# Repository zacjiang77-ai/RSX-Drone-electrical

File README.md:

# RSX Jetson 19 V buck converter

This is a standalone daughterboard for the protected 6S branch of the RSX PDB. Open `RSX_Jetson_19V.kicad_pro` in KiCad 9 or later. Keep both project library tables and the project-local symbol and footprint libraries alongside the project.

| Parameter | Design value |
| --- | --- |
| Input at U1 under load | 19.8–25.2 V DC |
| Output | 19.0 V nominal |
| Jetson load assumption | 2.37 A, 45.0 W |
| Power-stage design target | 3.0 A, 57 W |
| Topology | LM70880RRXR synchronous buck |
| Switching frequency | 220 kHz nominal with 100 kΩ at RT |
| Board | 64 × 39 mm, four copper layers, four 3.2 mm mounting holes |

## Wiring

- J1 pin 1 takes protected 6S VBAT. J1 pin 2 is ground. Use the upstream protection and cutoff provided by the PDB. U1 EN follows the input and supplies no separate 6S cutoff.
- J2 pin 1 supplies +19 V to the center contact of the Jetson cable. J2 pin 2 goes to the barrel sleeve. Verify polarity at the actual cable before plugging in the Jetson.
- The board assumes the specified 19.8 V minimum at the regulator pins after cable and PDB losses.

## Design calculations

- Feedback setpoint is 0.8 V × (1 + 232 kΩ / 10.2 kΩ) = 18.996 V nominal.
- TI's off-time equation gives 19.59 V at 240 kHz and 126 ns. At 19.8 V there is approximately 0.21 V of margin before conduction losses, setpoint tolerance and ripple. In low-dropout mode the regulator can skip off cycles. Steady regulation at the 3 A target remains subject to bench validation.
- L1 is 33 µH nominal, with a specified maximum DCR of 20.7 mΩ at 25 °C. Ideal inductor ripple at 25.2 V is about 0.64 A peak-to-peak at 220 kHz and nominal inductance. U1 senses across the 10 mΩ shunt with separate Kelvin connections. The nominal cycle-by-cycle threshold is 5.6 A of peak inductor current.
- The Type II compensation network starts at 8.06 kΩ, 33 nF and 820 pF. It targets approximately 5.4 kHz crossover using TI's simplified calculation with 120 µF effective output capacitance. Actual DC bias, ESR and crossover need verification with the assembled output network.
- SW4 is internally connected to the switching node and is routed locally to the bootstrap capacitor. The main switch path uses SW1 through SW3.

## Layout and bring-up

1. Review the RRX0029B land pattern and stencil with the assembler. Specify filled and capped vias where they are inside solderable pads, including the ground thermal pad. Align L1's marked winding-start terminal with pad 1 toward U1.
2. Use a current-limited bench source and an electronic load. Start at 22.2 V and verify polarity, startup, and no-load output. Sweep input from 25.2 V to 19.8 V while checking 2.37 A and then the 3 A design target.
3. Scope VIN at U1 and VOUT at the Jetson cable during input and load steps. Check ripple, hot operation, loop response and recovery near dropout. Keep startup and unload peaks below the Jetson's 20 V DC jack maximum. Verify with the real battery, PDB and cable before flight.

KiCad 9.0.2 ERC, board DRC and schematic parity checks pass. Hardware testing is pending.

## References

- [TI LM70880 datasheet and RRX0029B package drawing](https://www.ti.com/lit/ds/symlink/lm70880.pdf)
- [Coilcraft XGL1313-333 inductor specifications and land pattern](https://www.coilcraft.com/en-us/products/power/high-voltage-inductors/xgl/xgl1313/xgl1313-333/)
- [NVIDIA Jetson Orin Nano developer kit carrier board specification](https://developer.nvidia.com/downloads/assets/embedded/secure/jetson/orin_nano/docs/jetson_orin_nano_devkit_carrier_board_specification_sp.pdf)

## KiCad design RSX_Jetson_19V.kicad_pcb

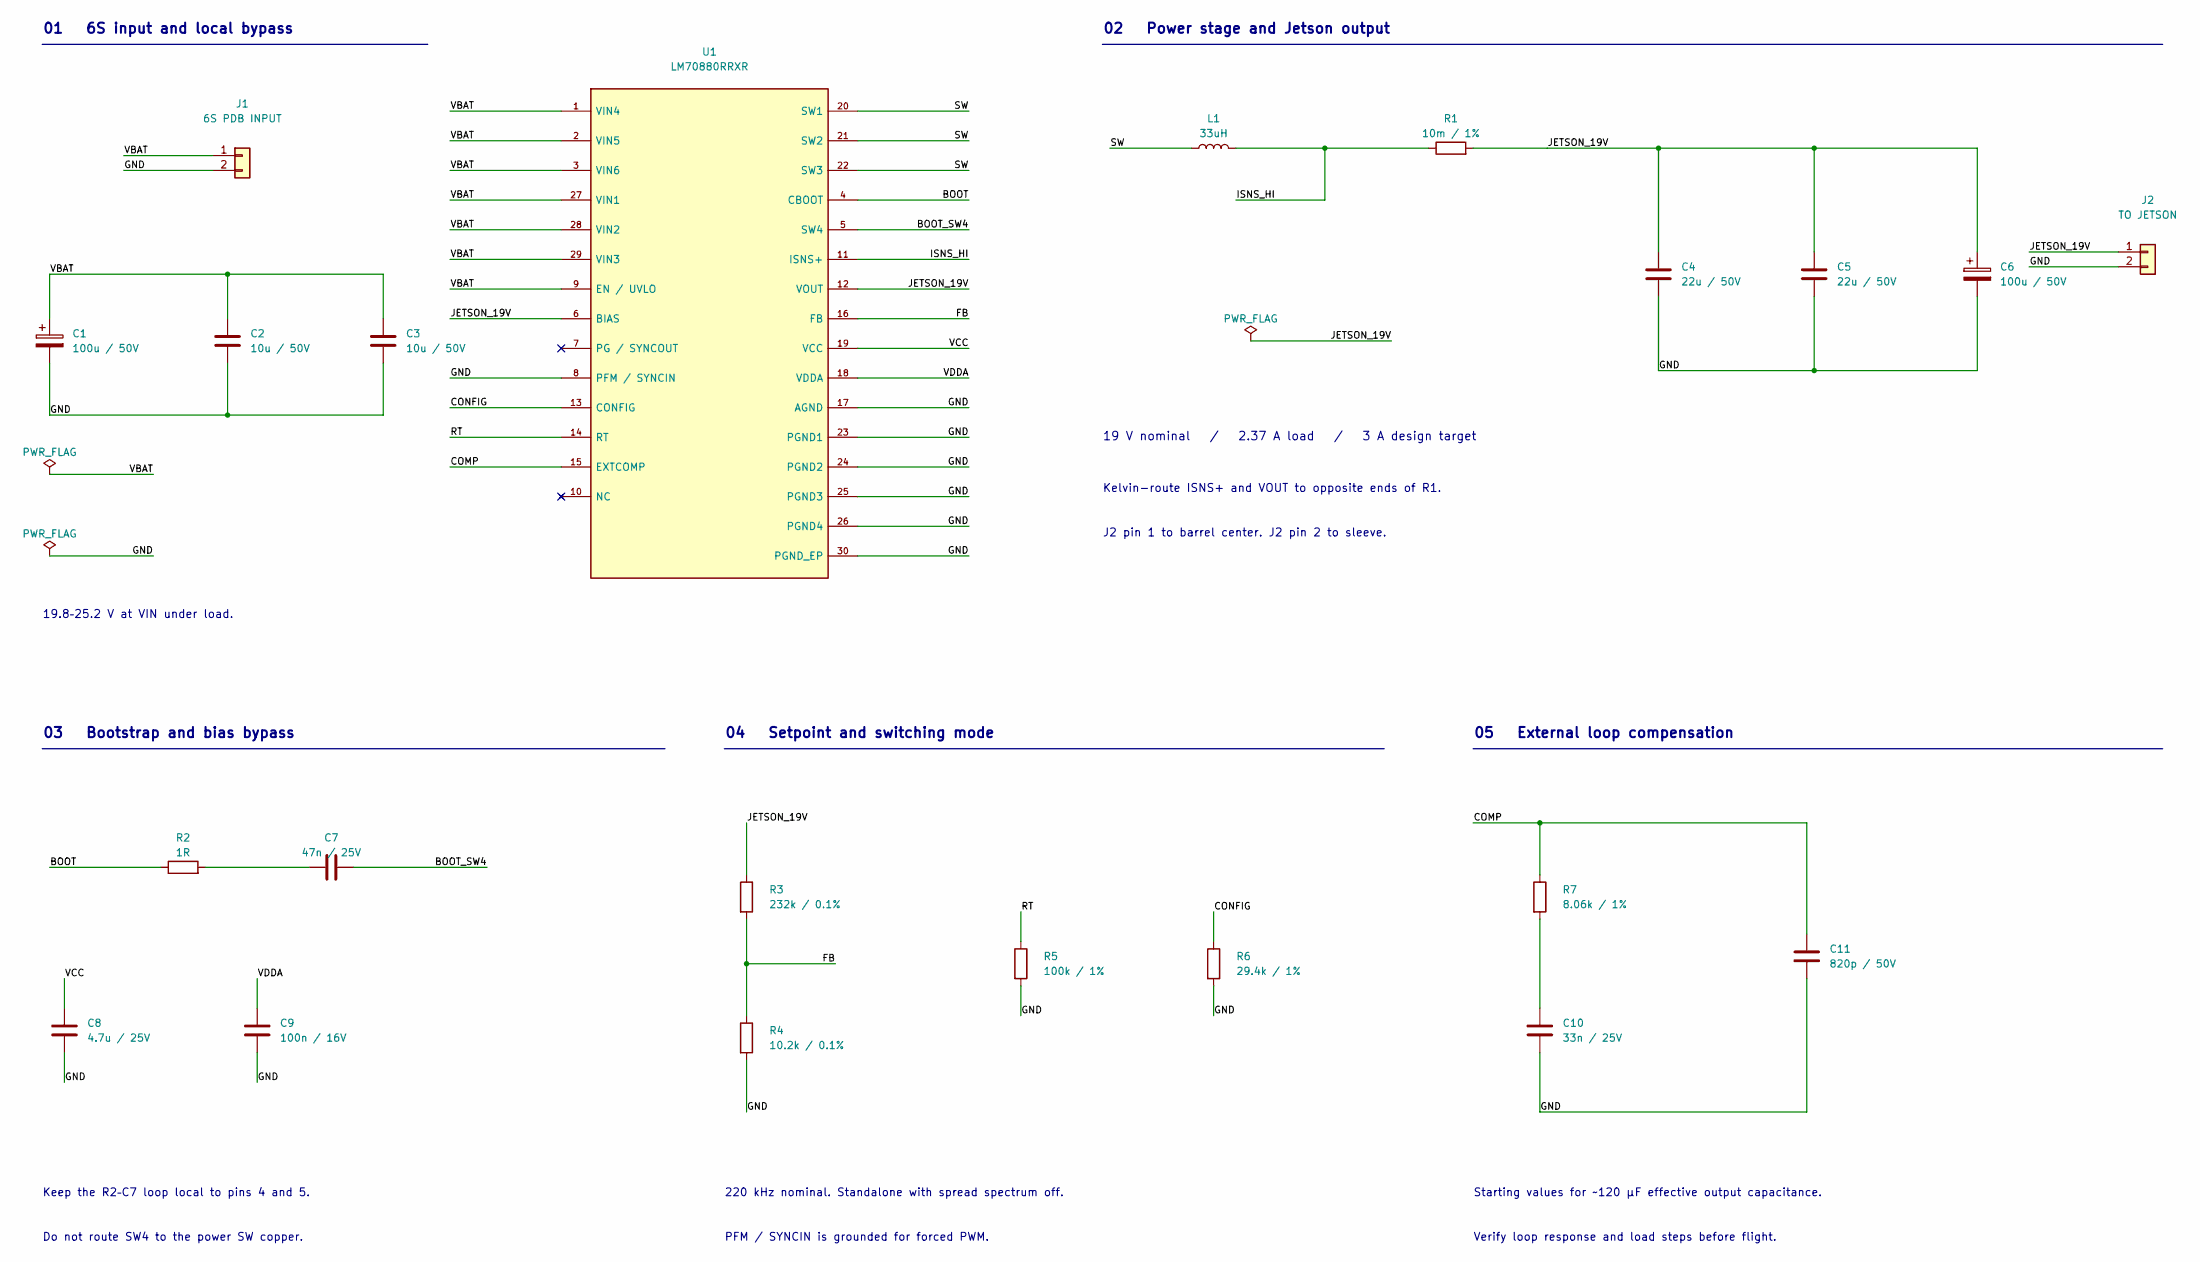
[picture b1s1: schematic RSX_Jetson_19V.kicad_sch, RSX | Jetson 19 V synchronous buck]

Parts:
C1, C6: 100u / 50V; CP_Elec_10x10.5; MPN EEHZA1H101P
C2, C3: 10u / 50V; C_1210_3225Metric; MPN C3225X7R1H106K250AC
C4, C5: 22u / 50V; C_1210_3225Metric; MPN C3225X7R1H226M250AC
C7: 47n / 25V; C_0603_1608Metric
C8: 4.7u / 25V; C_0805_2012Metric
C9: 100n / 16V; C_0603_1608Metric
C10: 33n / 25V; C_0603_1608Metric
C11: 820p / 50V; C_0603_1608Metric
J1: 6S PDB INPUT; TerminalBlock_Phoenix_MKDS-1,5-2-5.08_1x02_P5.08mm_Horizont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; MPN 1715721
J2: TO JETSON; TerminalBlock_Phoenix_MKDS-1,5-2-5.08_1x02_P5.08mm_Horizont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; MPN 1715721
L1: 33uH; Coilcraft_XGL1313; MPN XGL1313-333MED
R1: 10m / 1%; R_2512_6332Metric; MPN WSL2512R0100FEA
R2: 1R; R_0603_1608Metric
R3: 232k / 0.1%; R_0603_1608Metric
R4: 10.2k / 0.1%; R_0603_1608Metric
R5: 100k / 1%; R_0603_1608Metric
R6: 29.4k / 1%; R_0603_1608Metric
R7: 8.06k / 1%; R_0603_1608Metric
U1: LM70880RRXR; TI_RRX0029B; MPN LM70880RRXR

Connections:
/BOOT: R2.1, U1.4 (CBOOT)
/BOOT_SW4: C7.2, U1.5 (SW4)
/COMP: C11.1, R7.1, U1.15 (EXTCOMP)
/CONFIG: R6.1, U1.13 (CONFIG)
/FB: R3.2, R4.1, U1.16 (FB)
/GND: C1.2, C2.2, C3.2, C4.2, C5.2, C6.2, C8.2, C9.2, C10.2, C11.2, J1.2, J2.2, R4.2, R5.2, R6.2, U1.8 (PFM / SYNCIN), U1.17 (AGND), U1.23 (PGND1), U1.24 (PGND2), U1.25 (PGND3), U1.26 (PGND4), U1.30 (PGND_EP)
/ISNS_HI: L1.2, R1.1, U1.11 (ISNS+)
/JETSON_19V: C4.1, C5.1, C6.1, J2.1, R1.2, R3.1, U1.6 (BIAS), U1.12 (VOUT)
/RT: R5.1, U1.14 (RT)
/SW: L1.1, U1.20 (SW1), U1.21 (SW2), U1.22 (SW3)
/VBAT: C1.1, C2.1, C3.1, J1.1, U1.1 (VIN4), U1.2 (VIN5), U1.3 (VIN6), U1.9 (EN / UVLO), U1.27 (VIN1), U1.28 (VIN2), U1.29 (VIN3)
/VCC: C8.1, U1.19 (VCC)
/VDDA: C9.1, U1.18 (VDDA)
unnamed: C7.1, R2.2
unnamed: C10.1, R7.2

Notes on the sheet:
01 6S input and local bypass
19.8–25.2 V at VIN under load.
02 Power stage and Jetson output
19 V nominal / 2.37 A load / 3 A design target
Kelvin-route ISNS+ and VOUT to opposite ends of R1.
J2 pin 1 to barrel center. J2 pin 2 to sleeve.
03 Bootstrap and bias bypass
Keep the R2–C7 loop local to pins 4 and 5.
Do not route SW4 to the power SW copper.
04 Setpoint and switching mode
220 kHz nominal. Standalone with spread spectrum off.
PFM / SYNCIN is grounded for forced PWM.
05 External loop compensation
Starting values for ~120 µF effective output capacitance.
Verify loop response and load steps before flight.

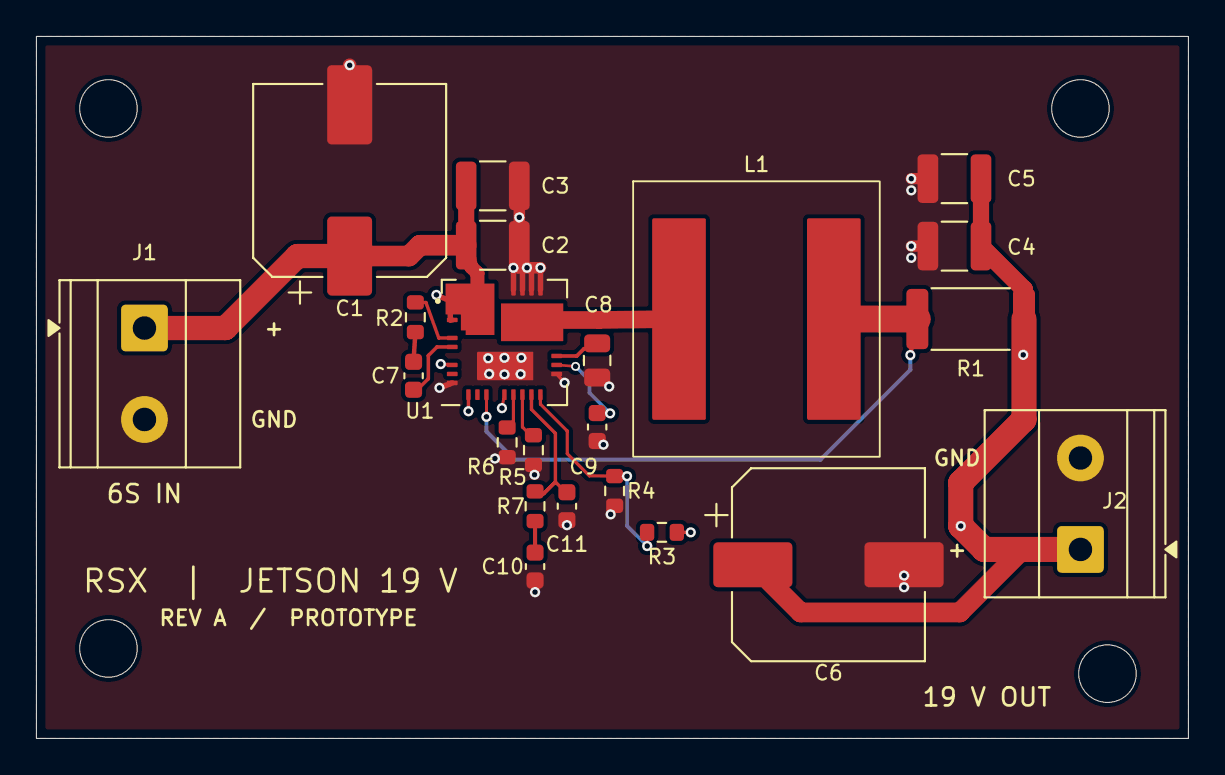
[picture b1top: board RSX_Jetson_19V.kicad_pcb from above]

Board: 4 copper layers, 64.0 x 39.0 mm, 26 parts (0 on the bottom side), 15 nets.

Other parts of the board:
H1, H2, H3, H4: MountingHole_3.2mm_M3

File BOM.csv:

"Refs","Value","MPN","Footprint","Qty"
"C1,C6","100u / 50V","EEHZA1H101P","Capacitor_SMD:CP_Elec_10x10.5","2"
"C2,C3","10u / 50V","C3225X7R1H106K250AC","Capacitor_SMD:C_1210_3225Metric","2"
"C4,C5","22u / 50V","C3225X7R1H226M250AC","Capacitor_SMD:C_1210_3225Metric","2"
"C7","47n / 25V","","Capacitor_SMD:C_0603_1608Metric","1"
"C8","4.7u / 25V","","Capacitor_SMD:C_0805_2012Metric","1"
"C9","100n / 16V","","Capacitor_SMD:C_0603_1608Metric","1"
"C10","33n / 25V","","Capacitor_SMD:C_0603_1608Metric","1"
"C11","820p / 50V","","Capacitor_SMD:C_0603_1608Metric","1"
"J1","6S PDB INPUT","1715721","TerminalBlock_Phoenix:TerminalBlock_Phoenix_MKDS-1,5-2-5.08_1x02_P5.08mm_Horizontal","1"
"J2","TO JETSON","1715721","TerminalBlock_Phoenix:TerminalBlock_Phoenix_MKDS-1,5-2-5.08_1x02_P5.08mm_Horizontal","1"
"L1","33uH","XGL1313-333MED","RSX_Jetson:Coilcraft_XGL1313","1"
"R1","10m / 1%","WSL2512R0100FEA","Resistor_SMD:R_2512_6332Metric","1"
"R2","1R","","Resistor_SMD:R_0603_1608Metric","1"
"R3","232k / 0.1%","","Resistor_SMD:R_0603_1608Metric","1"
"R4","10.2k / 0.1%","","Resistor_SMD:R_0603_1608Metric","1"
"R5","100k / 1%","","Resistor_SMD:R_0603_1608Metric","1"
"R6","29.4k / 1%","","Resistor_SMD:R_0603_1608Metric","1"
"R7","8.06k / 1%","","Resistor_SMD:R_0603_1608Metric","1"
"U1","LM70880RRXR","LM70880RRXR","RSX_Jetson:TI_RRX0029B","1"
